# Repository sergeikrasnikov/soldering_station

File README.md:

The article about the project you can find here 
[http://e1ectro.blogspot.ru/2017/02/diy-desoldering-station-for-25.html](http://e1ectro.blogspot.ru/2017/02/diy-desoldering-station-for-25.html)

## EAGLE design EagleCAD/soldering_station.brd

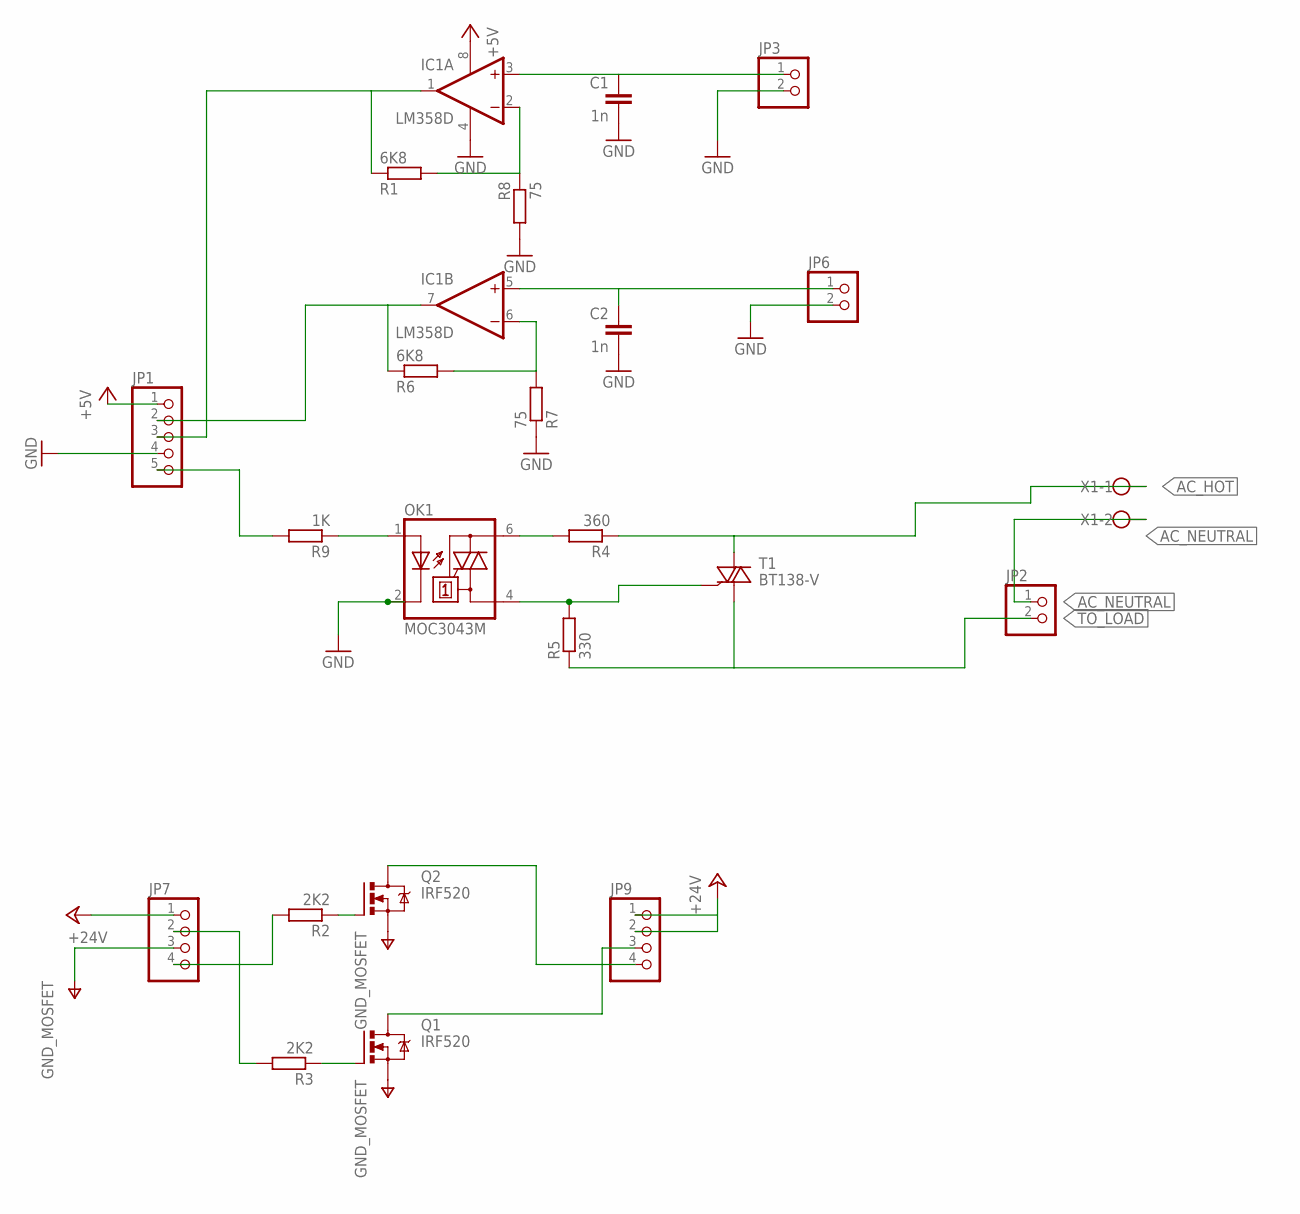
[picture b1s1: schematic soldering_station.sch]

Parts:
C1, C2: 1n; C0805
IC1: LM358D; SO08
JP1: PINHD-1X5; 1X05
JP2, JP3, JP6: PINHD-1X2; 1X02
JP7, JP9: PINHD-1X4; 1X04
OK1: MOC3043M; DIL06
Q1, Q2: IRF520; TO220BV
R1, R6: 6K8; R0805
R2, R3: 2K2; R0805
R4: 360; R0805
R5: 330; R0805
R7, R8: 75; R0805
R9: 1K; R0805
T1: BT138-V; TO220BV
X1: W237-102

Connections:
+5V: IC1.8 (V+), JP1.1
+24V: JP7.1, JP9.1, JP9.2
AC_HOT: R4.1, T1.T2 (A2), X1.1
AC_NEUTRAL: JP2.1, X1.2
GND: C1.2, C2.2, IC1.4 (V-), JP1.4, JP3.2, JP6.2, OK1.2 (C), R7.1, R8.2
unnamed: C1.1, IC1.3 (+IN), JP3.1
unnamed: IC1.1 (OUT), JP1.3, R1.1
unnamed: IC1.2 (-IN), R1.2, R8.1
unnamed: IC1.7 (OUT), JP1.2, R6.1
unnamed: IC1.6 (-IN), R6.2, R7.2
unnamed: Q1.G, R3.1
unnamed: Q2.G, R2.1
unnamed: OK1.6 (A2), R4.2
unnamed: OK1.4 (A1), R5.2, T1.G
unnamed: OK1.1 (A), R9.1
unnamed: JP1.5, R9.2
unnamed: C2.1, IC1.5 (+IN), JP6.1
unnamed: JP7.4, R2.2
unnamed: JP7.2, R3.2
unnamed: JP9.4, Q2.D
unnamed: JP9.3, Q1.D
TO_LOAD: JP2.2, R5.1, T1.T1 (A1)
V-: JP7.3, Q1.S, Q2.S

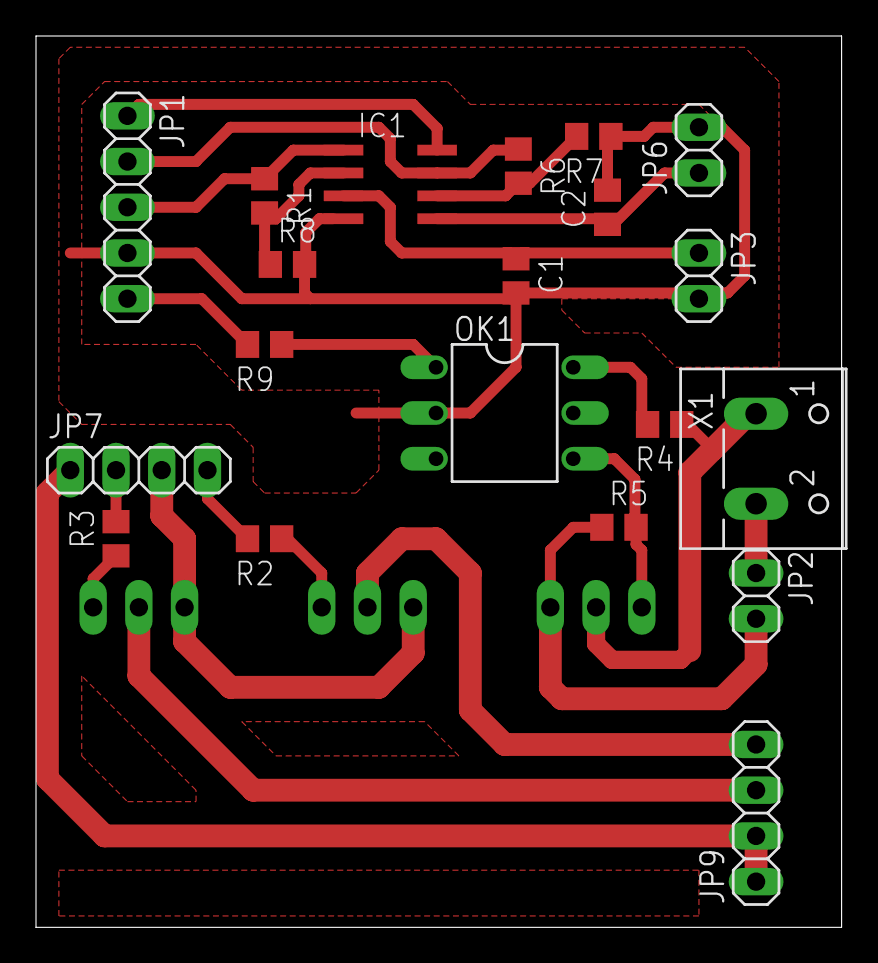
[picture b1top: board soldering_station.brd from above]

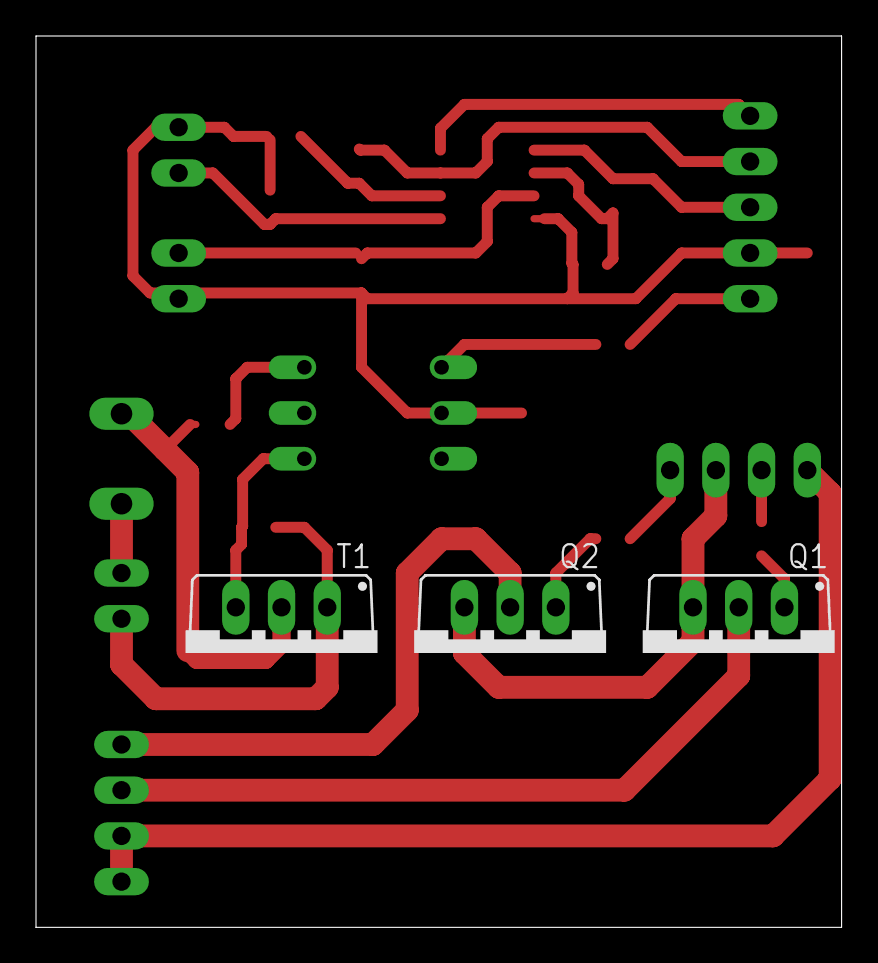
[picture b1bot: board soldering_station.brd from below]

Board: 2 copper layers, 44.8 x 49.5 mm, 23 parts (3 on the bottom side), 23 nets.
